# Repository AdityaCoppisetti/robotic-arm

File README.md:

# 6-Axis Robotic Arm

This project is a custom-built 6-axis robotic arm that I designed and built from the ground up. 
The arm has six degrees of freedom thus the 6DOF , I designed the mechanical parts myself and used a combination of 3D printing, custom gears ,and  almost each joint is a planetary mechanism since i really wanted to learn that and i learnt that in onshape .  The gripper usse MG996R V17 servo

The control side of the project is a custom pcb which is handled by a custom arduino uno nano that i made . the main pcb usees a4988 stepper motor drivers to drive each and every motor and the servo motor for the gripper i have connected directly . The plan is to use forward and inverse kinematics to move to a specific point instead of manually controlling every joint.

One of the things I want to experiment with later is turning the arm into a 3D printer by replacing the gripper with a printing head. This would make the robot more than just a robotic arm and i could then print alot of stuff from a arm that itself was 3d printed bahahahhahahaa

 There will probably be a lot of redesigns, and ill keep updating the journal.md of this repo for that 

i designed this robotic arm in onshape, 

joint 1 - 5 uses planetary gear mechanism where the sun gear is attached to the nema 17 motor

and then ive made the claw/ gripper 
which uses a servo motor attached to a spur gear which move yet 2 another spur gears

# how to assemble 

print the given step files , modify them if you want to 

and then look at the assembled version and piece everything together. i will be documenting my proccess aswell when i print the parts. 

# how to assemble electronic part of project

when you get the main pcb and then the microcontroller pcb
you take the stencil and then use that stencil to apply solder paste. 
and then you remove the stencil and place each component by looking at the nicely labelled pcb 

and then by using a hot air gun or a hotplate , reflow the solder 

# hot to assemble the main board pcb 

you take the pcb and using a soldering iron just solder the required amount of female or male pinheaders ( 2.57mm exactly) 

here is a mockup i nade using onshape of how the main pcb should look like after you assemlbe it

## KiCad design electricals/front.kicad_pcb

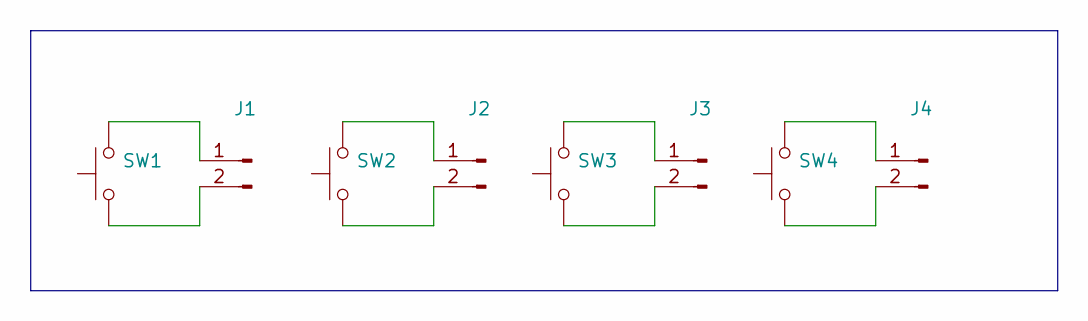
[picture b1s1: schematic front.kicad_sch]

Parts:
J1, J2, J3, J4: Conn_01x02_Pin; PinHeader_1x02_P1.00mm_Vertical
SW1, SW2, SW3, SW4: SW_Push; SW_Cherry_MX_PCB_1.00u

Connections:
unnamed: J1.1, SW1.2
unnamed: J1.2, SW1.1
unnamed: J2.1, SW2.2
unnamed: J2.2, SW2.1
unnamed: J3.1, SW3.2
unnamed: J3.2, SW3.1
unnamed: J4.1, SW4.2
unnamed: J4.2, SW4.1

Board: 2 copper layers, 8 parts (0 on the bottom side), 8 nets, no tracks yet.

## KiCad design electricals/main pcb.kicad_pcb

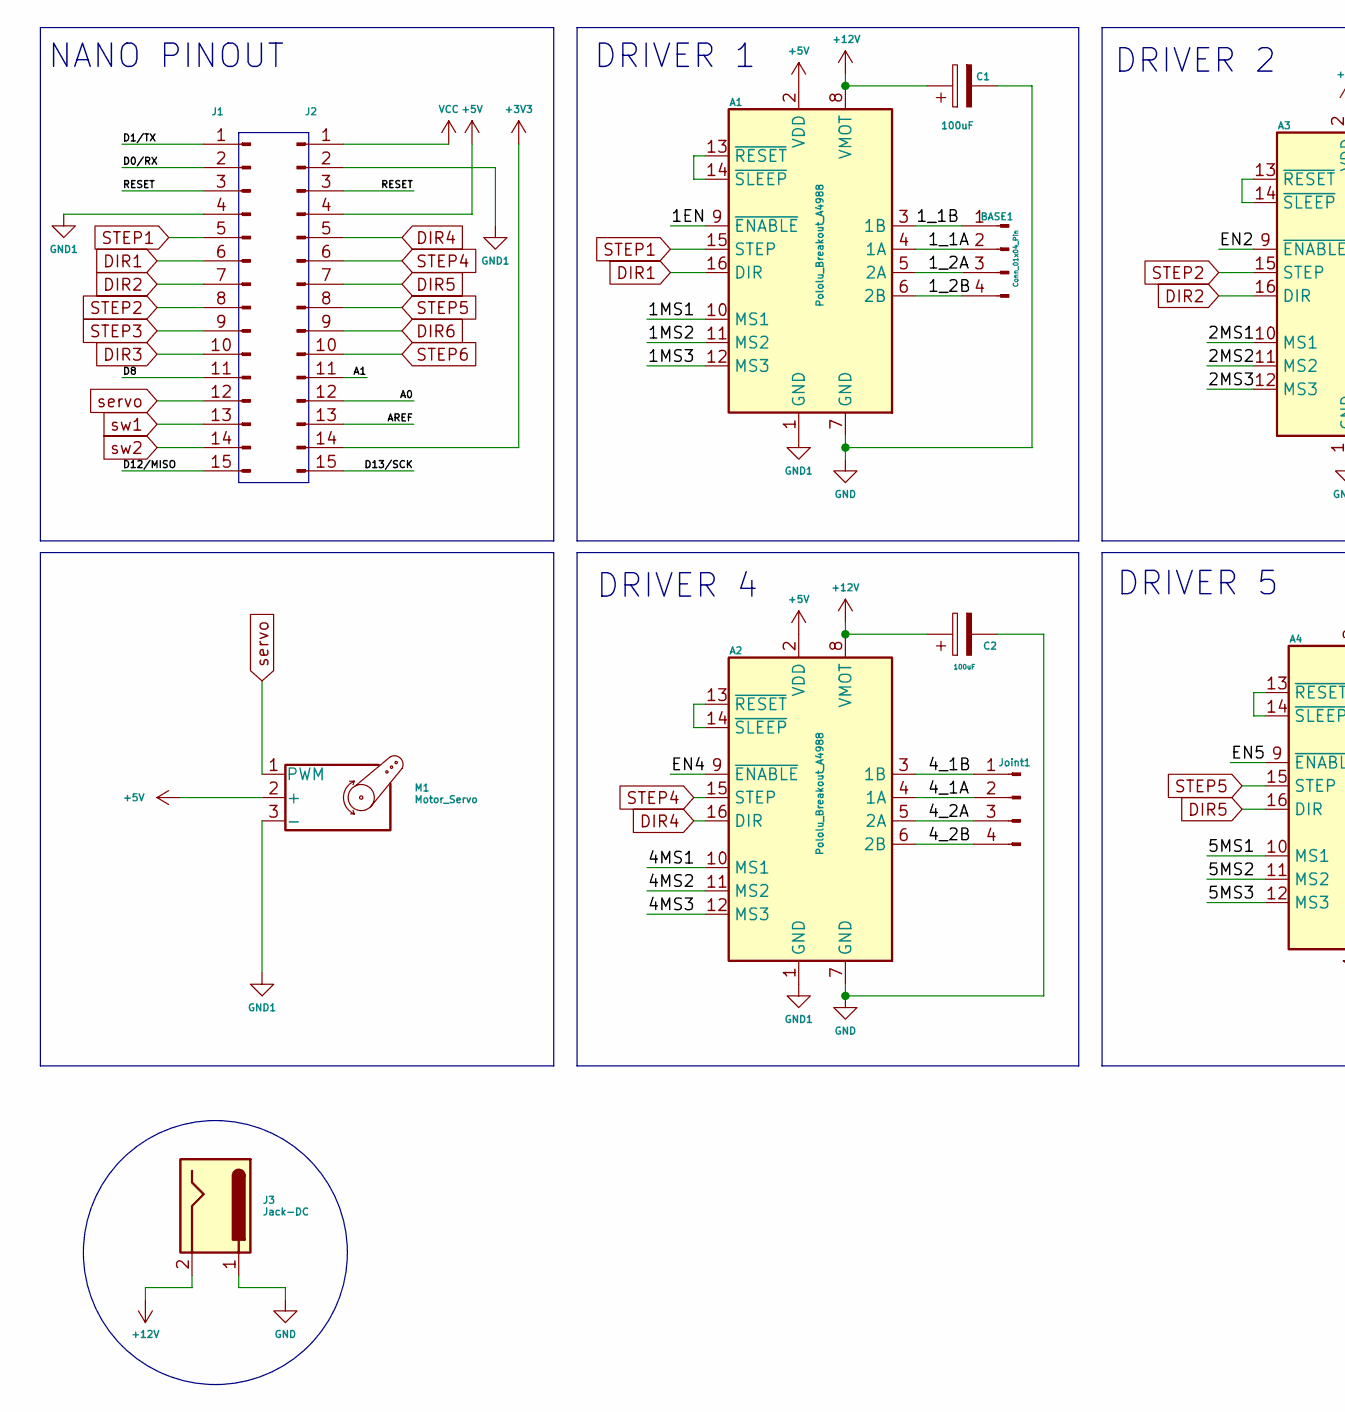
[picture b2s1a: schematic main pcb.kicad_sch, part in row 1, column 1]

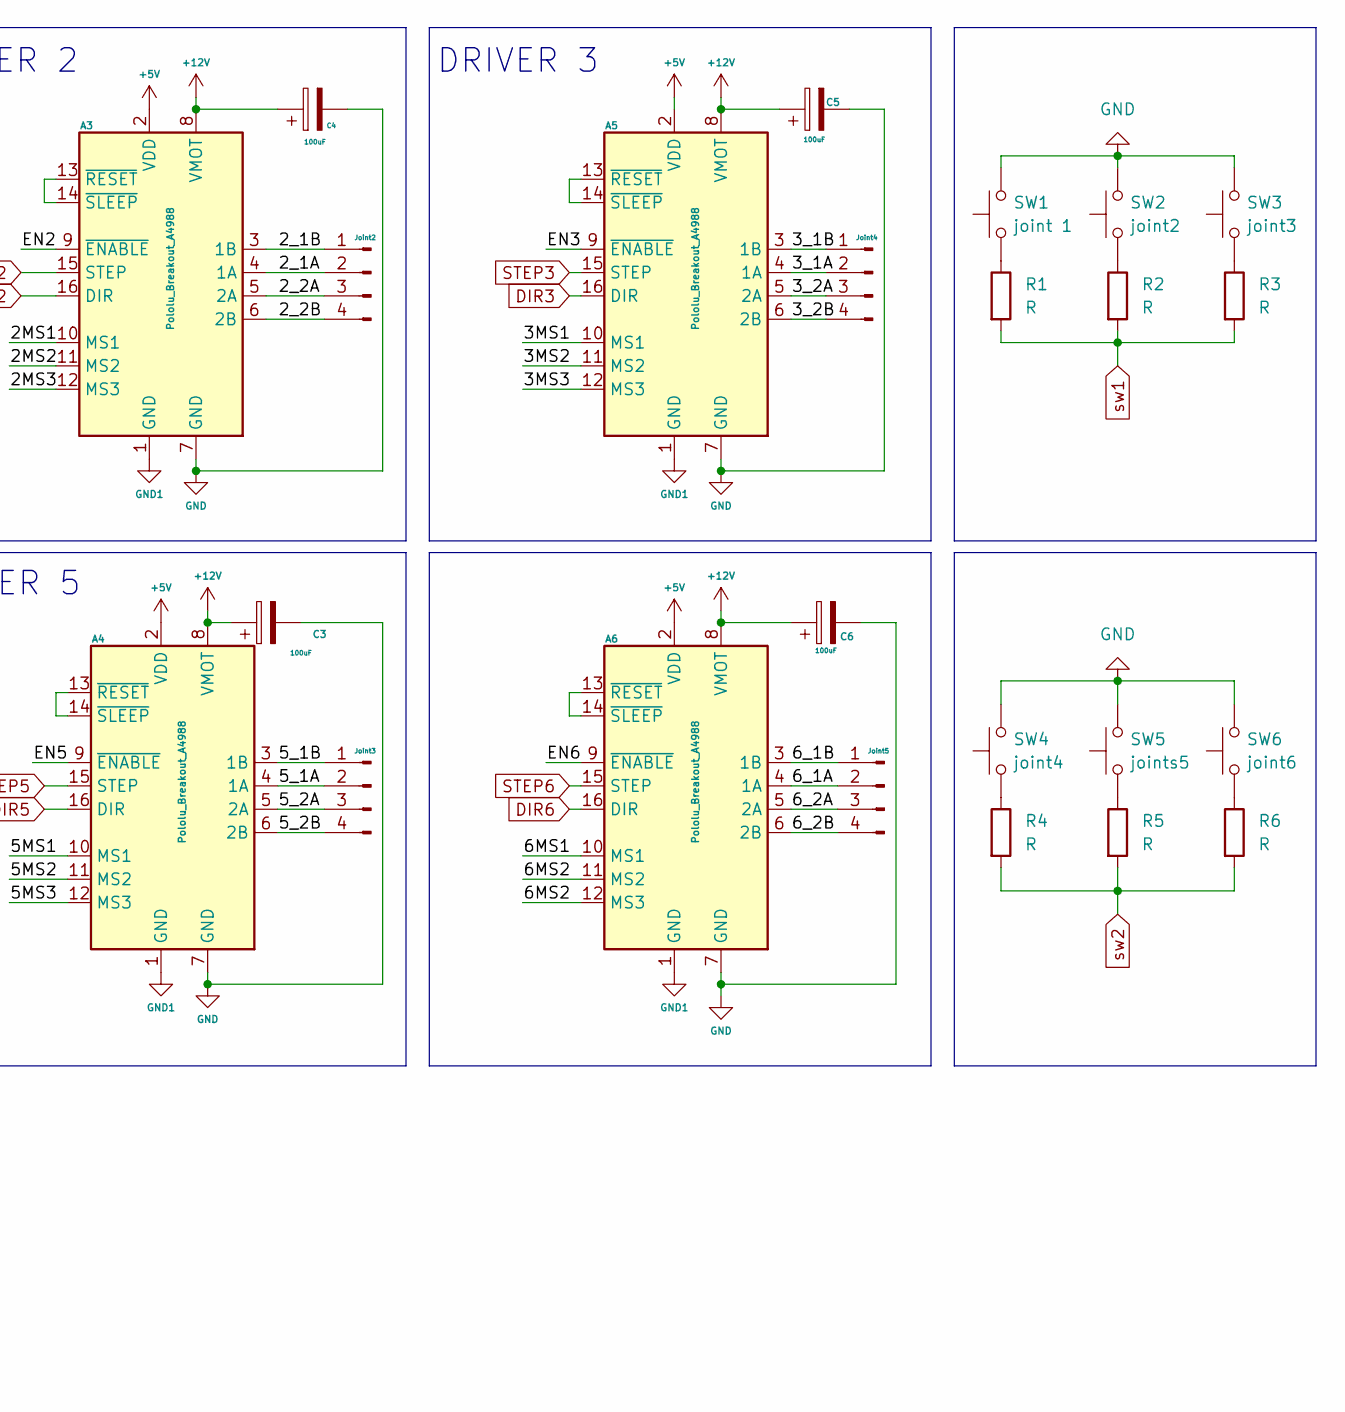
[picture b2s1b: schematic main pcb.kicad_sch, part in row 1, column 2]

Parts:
A1, A2, A3, A4, A5, A6: Pololu_Breakout_A4988; Pololu_Breakout-16_15.2x20.3mm
BASE1: Conn_01x04_Pin; PinHeader_1x04_P2.00mm_Vertical
C1, C2, C3, C4, C5, C6: 100uF; CP_Radial_D8.0mm_P3.50mm
J1, J2: Conn_01x15_Pin; PinHeader_1x15_P2.54mm_Vertical
J3: Jack-DC; PinSocket_1x02_P2.54mm_Vertical
Joint1, Joint2, Joint3, Joint4, Joint5: Conn_01x04_Pin; PinHeader_1x04_P2.00mm_Vertical
M1: Motor_Servo; PinHeader_1x03_P2.54mm_Vertical
R1, R2, R3, R4, R5, R6: R; PinHeader_1x02_P2.54mm_Vertical
SW1: joint 1; PinHeader_1x02_P1.27mm_Vertical
SW2: joint2; PinHeader_1x02_P1.27mm_Vertical
SW3: joint3; PinHeader_1x02_P1.27mm_Vertical
SW4: joint4; PinHeader_1x02_P1.27mm_Vertical
SW5: joints5; PinHeader_1x02_P1.27mm_Vertical
SW6: joint6; PinHeader_1x02_P1.27mm_Vertical

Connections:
+3V3: J2.14
+5V: A1.2 (VDD), A2.2 (VDD), A3.2 (VDD), A4.2 (VDD), A5.2 (VDD), A6.2 (VDD), J2.4, M1.2 (+)
+12V: A1.8 (VMOT), A2.8 (VMOT), A3.8 (VMOT), A4.8 (VMOT), A5.8 (VMOT), A6.8 (VMOT), C1.1, C2.1, C3.1, C4.1, C5.1, C6.1, J3.2
/1EN: A1.9 (~ENABLE)
/1MS1: A1.10 (MS1)
/1MS2: A1.11 (MS2)
/1MS3: A1.12 (MS3)
/1_1A: A1.4 (1A), BASE1.2
/1_1B: A1.3 (1B), BASE1.1
/1_2A: A1.5 (2A), BASE1.3
/1_2B: A1.6 (2B), BASE1.4
/2MS1: A3.10 (MS1)
/2MS2: A3.11 (MS2)
/2MS3: A3.12 (MS3)
/2_1A: A3.4 (1A), Joint2.2
/2_1B: A3.3 (1B), Joint2.1
/2_2A: A3.5 (2A), Joint2.3
/2_2B: A3.6 (2B), Joint2.4
/3MS1: A5.10 (MS1)
/3MS2: A5.11 (MS2)
/3MS3: A5.12 (MS3)
/3_1A: A5.4 (1A), Joint4.2
/3_1B: A5.3 (1B), Joint4.1
/3_2A: A5.5 (2A), Joint4.3
/3_2B: A5.6 (2B), Joint4.4
/4MS1: A2.10 (MS1)
/4MS2: A2.11 (MS2)
/4MS3: A2.12 (MS3)
/4_1A: A2.4 (1A), Joint1.2
/4_1B: A2.3 (1B), Joint1.1
/4_2A: A2.5 (2A), Joint1.3
/4_2B: A2.6 (2B), Joint1.4
/5MS1: A4.10 (MS1)
/5MS2: A4.11 (MS2)
/5MS3: A4.12 (MS3)
/5_1A: A4.4 (1A), Joint3.2
/5_1B: A4.3 (1B), Joint3.1
/5_2A: A4.5 (2A), Joint3.3
/5_2B: A4.6 (2B), Joint3.4
/6MS1: A6.10 (MS1)
/6MS2: A6.11 (MS2), A6.12 (MS3)
/6_1A: A6.4 (1A), Joint5.2
/6_1B: A6.3 (1B), Joint5.1
/6_2A: A6.5 (2A), Joint5.3
/6_2B: A6.6 (2B), Joint5.4
/A0: J2.12
/A1: J2.11
/AREF: J2.13
/D0/RX: J1.2
/D1/TX: J1.1
/D8: J1.11
/D12/MISO: J1.15
/D13/SCK: J2.15
/EN2: A3.9 (~ENABLE)
/EN3: A5.9 (~ENABLE)
/EN4: A2.9 (~ENABLE)
/EN5: A4.9 (~ENABLE)
/EN6: A6.9 (~ENABLE)
/RESET: J1.3, J2.3
DIR1: A1.16 (DIR), J1.6
DIR2: A3.16 (DIR), J1.7
DIR3: A5.16 (DIR), J1.10
DIR4: A2.16 (DIR), J2.5
DIR5: A4.16 (DIR), J2.7
DIR6: A6.16 (DIR), J2.9
GND: A1.7 (GND), A2.7 (GND), A3.7 (GND), A4.7 (GND), A5.7 (GND), A6.7 (GND), C1.2, C2.2, C3.2, C4.2, C5.2, C6.2, J3.1, SW1.2, SW2.2, SW3.2, SW4.2, SW5.2, SW6.2
GND1: A1.1 (GND), A2.1 (GND), A3.1 (GND), A4.1 (GND), A5.1 (GND), A6.1 (GND), J1.4, J2.2, M1.3 (-)
unnamed: A1.13 (~RESET), A1.14 (~SLEEP)
unnamed: A2.13 (~RESET), A2.14 (~SLEEP)
unnamed: A3.13 (~RESET), A3.14 (~SLEEP)
unnamed: A4.13 (~RESET), A4.14 (~SLEEP)
unnamed: A5.13 (~RESET), A5.14 (~SLEEP)
unnamed: A6.13 (~RESET), A6.14 (~SLEEP)
unnamed: R1.1, SW1.1
unnamed: R2.1, SW2.1
unnamed: R3.1, SW3.1
unnamed: R4.1, SW4.1
unnamed: R5.1, SW5.1
unnamed: R6.1, SW6.1
STEP1: A1.15 (STEP), J1.5
STEP2: A3.15 (STEP), J1.8
STEP3: A5.15 (STEP), J1.9
STEP4: A2.15 (STEP), J2.6
STEP5: A4.15 (STEP), J2.8
STEP6: A6.15 (STEP), J2.10
VCC: J2.1
servo: J1.12, M1.1 (PWM)
sw1: J1.13, R1.2, R2.2, R3.2
sw2: J1.14, R4.2, R5.2, R6.2

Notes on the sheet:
DRIVER 5
DRIVER 2
DRIVER 4
DRIVER 1
NANO PINOUT
DRIVER 3

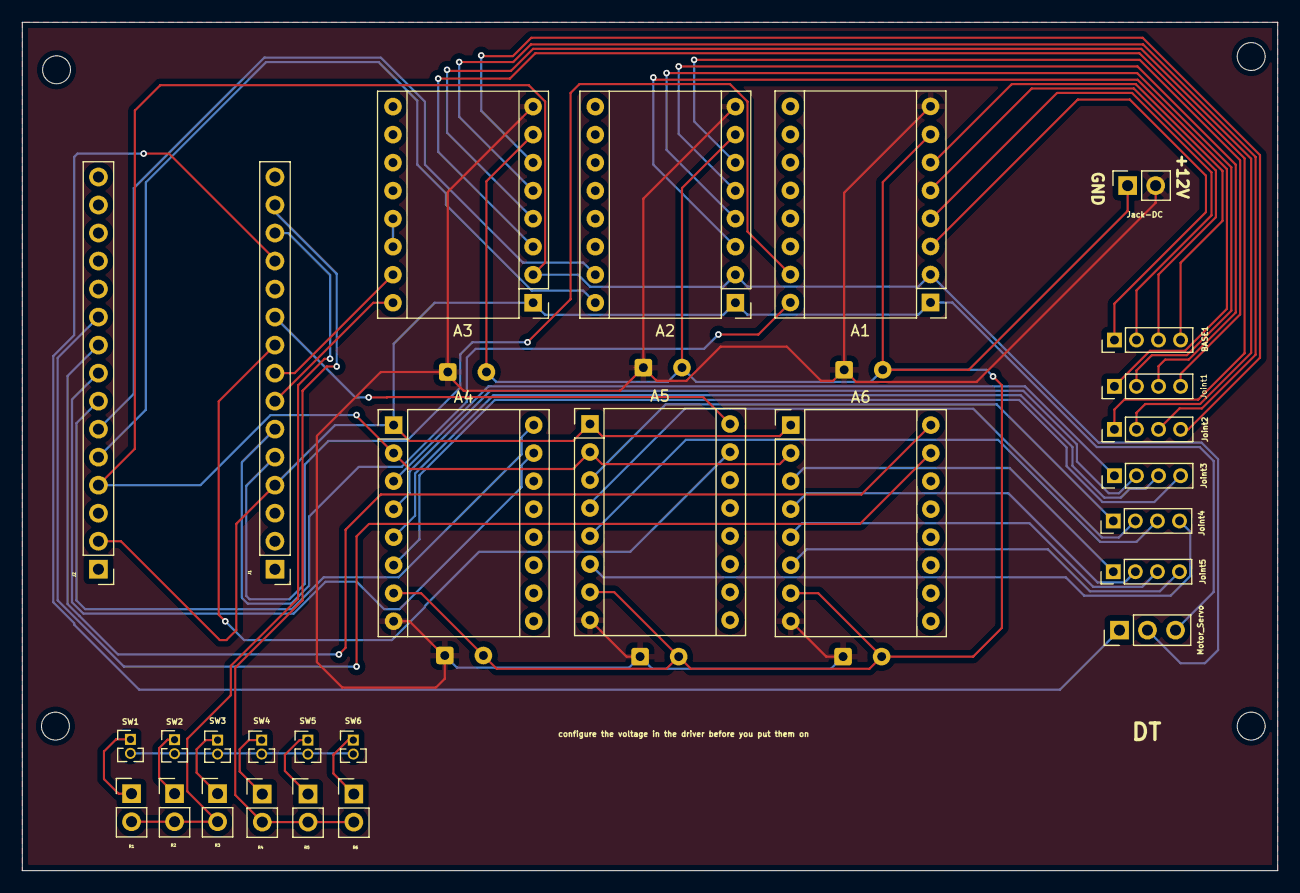
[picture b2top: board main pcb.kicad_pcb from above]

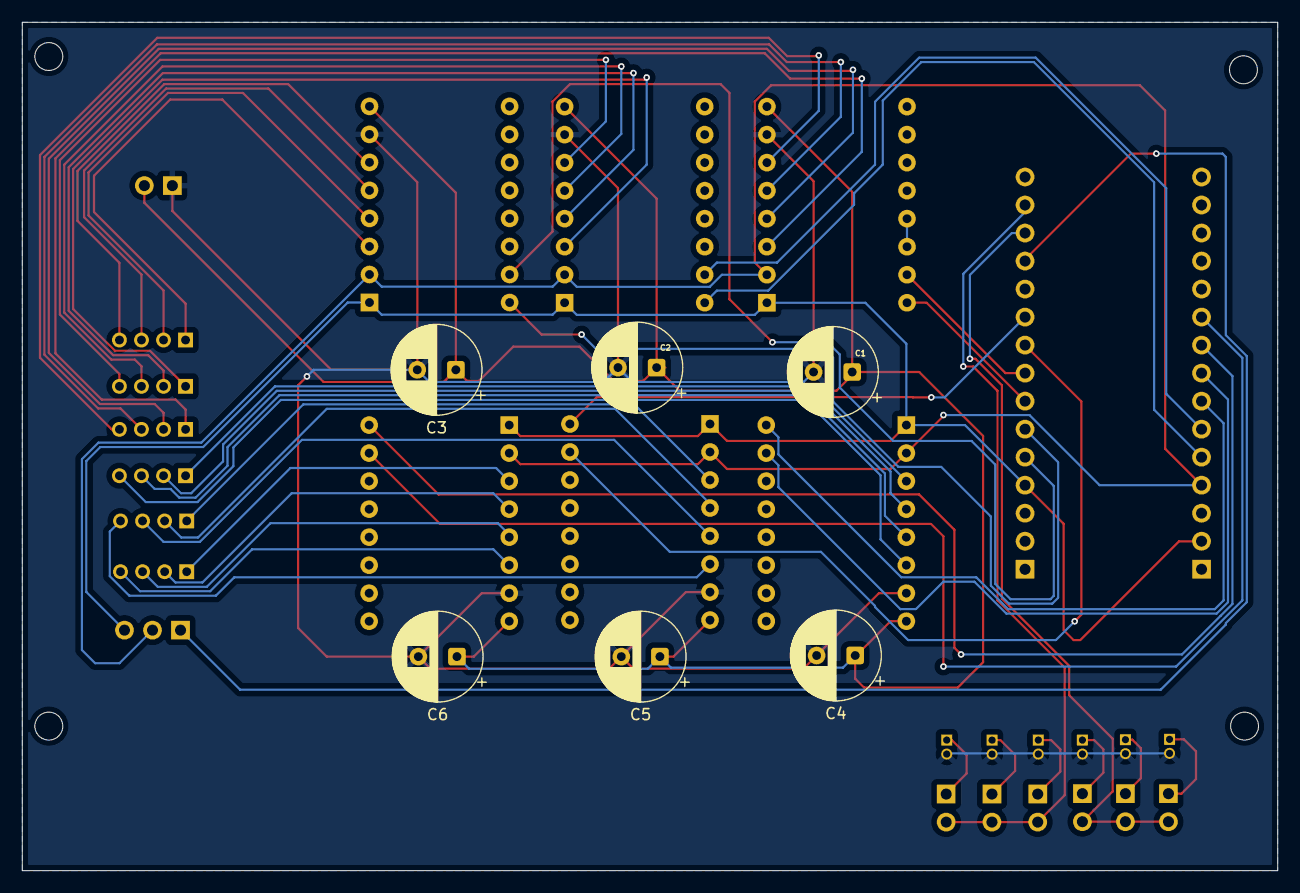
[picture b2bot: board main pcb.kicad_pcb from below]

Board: 2 copper layers, 113.8 x 76.9 mm, 34 parts (6 on the bottom side), 57 nets.

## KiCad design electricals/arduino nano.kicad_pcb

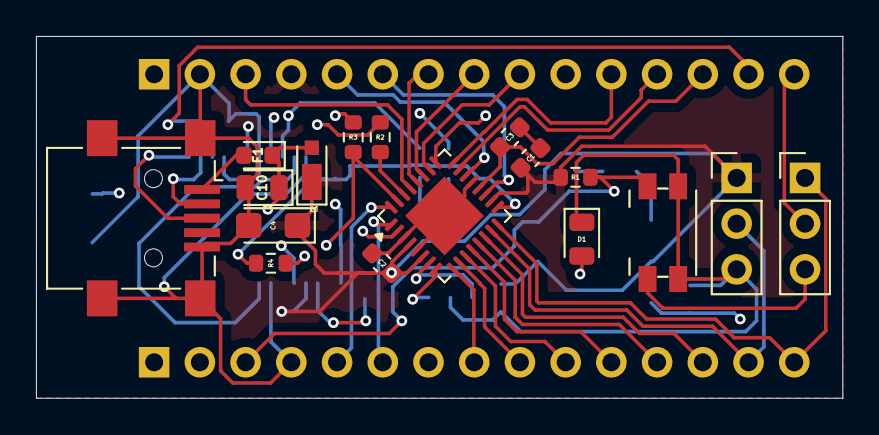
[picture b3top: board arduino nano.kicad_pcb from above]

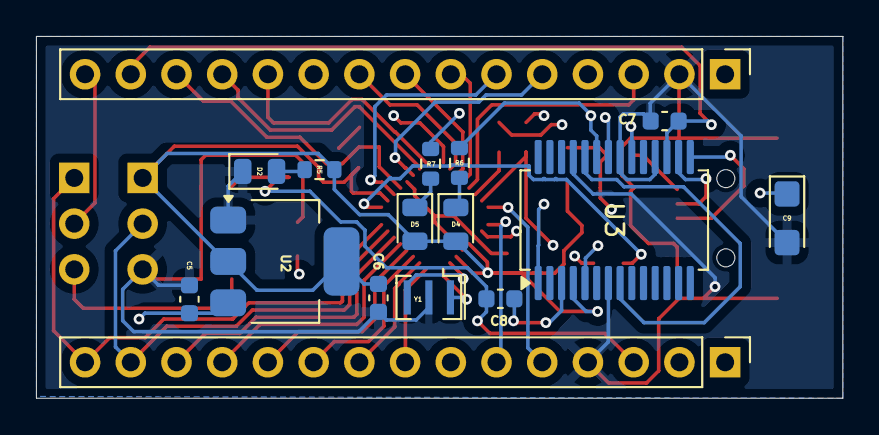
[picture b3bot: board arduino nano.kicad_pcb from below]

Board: 4 copper layers, 44.8 x 20.1 mm, 33 parts (16 on the bottom side), 43 nets.

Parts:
C1, C2, C5, C6: 1u; C_0603_1608Metric
C3, C7, C8: 100n; C_0603_1608Metric
C4, C9: 4u7_ 16V; CP_EIA-3216-10_Kemet-I
C10: 100n; LED_0805_2012Metric
D1: YELLOW; LED_0805_2012Metric
D2, D5: GREEN; LED_0805_2012Metric
D3: DIODE; D_MicroSMP_AK
D4: RED; LED_0805_2012Metric
F1: 0603; D_0603_1608Metric
J1: USB_B_Mini; USB_Mini-B_Lumberg_2486_01_Horizontal
J2, J4: Conn_01x15_Pin; PinHeader_1x15_P2.54mm_Vertical
J3: ICSP; PinHeader_1x03_P2.54mm_Vertical
J5: Conn_01x03_Pin; PinHeader_1x03_P2.54mm_Vertical
R1, R2, R3, R4, R5, R6, R7: 1K; R_0603_1608Metric
SW1: SW_Push; Panasonic_EVQPUK_EVQPUB
U1: ATmega328P-M; QFN-32-1EP_5x5mm_P0.5mm_EP3.1x3.1mm
U2: LM1117MP-5.0; SOT-223-3_TabPin2
U3: FT232RL; SSOP-28_5.3x10.2mm_P0.65mm
Y1: 16MHz; Resonator_SMD_Murata_CSTxExxV-3Pin_3.0x1.1mm

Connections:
+3V3: C7.1, J2.14, U3.17 (3V3OUT)
+5V: C1.1, C2.1, C4.1, C6.1, D3.1 (K), D4.2 (A), D5.2 (A), J2.4, J3.1, R1.1, R5.2, U1.4 (VCC), U1.6 (VCC), U1.18 (AVCC), U2.2 (VO), U3.4 (VCCIO), U3.20 (VCC)
/A0: J2.12, U1.23 (PC0)
/A1: J2.11, U1.24 (PC1)
/A2: J2.10, U1.25 (PC2)
/A3: J2.9, U1.26 (PC3)
/A4: J2.8, U1.27 (PC4)
/A5: J2.7, U1.28 (PC5)
/A6: J2.6, U1.19 (ADC6)
/A7: J2.5, U1.22 (ADC7)
/AREF: C3.1, J2.13, U1.20 (AREF)
/D1/TX: J4.1, R3.1, U1.31 (PD1)
/D2: J4.5, U1.32 (PD2)
/D3: J4.6, U1.1 (PD3)
/D4: J4.7, U1.2 (PD4)
/D5: J4.8, U1.9 (PD5)
/D6: J4.9, U1.10 (PD6)
/D7: J4.10, U1.11 (PD7)
/D8: J4.11, U1.12 (PB0)
/D9: J4.12, U1.13 (PB1)
/D10: J4.13, U1.14 (PB2)
/D11/MOSI: J3.2, J4.14, U1.15 (PB3)
/D12/MISO: J4.15, J5.1, U1.16 (PB4)
/D13/SCK: J2.15, J5.2, R4.2, U1.17 (PB5)
/DO/RX: R2.1, U1.30 (PD0)
/D_N: J1.2 (D-), U3.16 (USBD-)
/D_P: J1.3 (D+), U3.15 (USBD+)
/RESET: C8.1, J2.3, J4.3, J5.3, R1.2, SW1.1, U1.29 (~RESET/PC6)
/RX: R2.2, U3.5 (RXD)
/TX: R3.2, U3.1 (TXD)
/XTAL1: U1.7 (XTAL1/PB6), Y1.3
/XTAL2: U1.8 (XTAL2/PB7), Y1.1
GND: C1.2, C2.2, C3.2, C4.2, C5.2, C6.2, C7.2, C9.2, C10.2, D1.1 (K), D2.1 (K), J1.5 (GND), J1.6 (Shield), J2.2, J3.3, J4.4, SW1.2, U1.3 (GND), U1.5 (GND), U1.21 (GND), U1.33 (GND), U2.1 (GND), U3.7 (GND), U3.18 (GND), U3.21 (GND), U3.25 (AGND), Y1.2
unnamed: D1.2 (A), R4.1
unnamed: D2.2 (A), R5.1
unnamed: D4.1 (K), R6.1
unnamed: D5.1 (K), R7.1
unnamed: F1.2, J1.1 (VBUS)
unnamed: R6.2, U3.23 (CBUS0)
unnamed: R7.2, U3.22 (CBUS1)
unnamed: C8.2, U3.3 (RTS)
VBUS: C9.1, C10.1, D3.2 (A), F1.1
VCC: C5.1, J2.1, U2.3 (VI)
